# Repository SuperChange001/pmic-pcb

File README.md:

# Elastic Power Module

This repository contains the design and related files for the Elastic Power Module.

## Current Status
- [x] Schematic
- [x] PCB Design
- [x] Prototype
- [ ] Testing (** It is not tested yet, DO NOT use it as your reference design! **)
  - know issues:
    - in the default configuration, the nRST pin should be pulled up to VSYS, but right now it is floating.
      - should further check if I always need to have the external pull-up resistor or I can use the internal pull-up resistor of the microcontroller.
      - and how convinent it is to keep current circuit and configure the IC via microcontroller.
    - VIO should be connected to the header or a test pad, so we can configure the IC without flying a wire.

## Project Structure

- `elastic_power_module.kicad_pcb`: KiCad PCB design file.
- `elastic_power_module.kicad_prl`: KiCad project local settings file.
- `elastic_power_module.kicad_pro`: KiCad project file.
- `elastic_power_module.kicad_sch`: KiCad schematic file.
- `elastic_power_module.pdf`: PDF version of the schematic.
- `fp-info-cache`: Footprint info cache.
- `pictures`: Contains pictures of the assembled module.
  - `elastic_power_module_bottom_view.jpg`: Bottom view of the module.
  - `elastic_power_module_side_view.jpg`: Side view of the module.
  - `elastic_power_module_top_view.jpg`: Top view of the module.~

## Getting Started

- To get started with this project, clone the repository and open the `.kicad_pcb` or `.kicad_sch` files in KiCad.
- Or you can just download the PDF version of the schematic and use it as your reference design.
- To assemble the module, you can use the interactive BOM file [here](https://htmlpreview.github.io/?https://github.com/SuperChange001/pmic-pcb/blob/master/bom/ibom.html).

## Contributing

Contributions are welcome. Please open an issue to discuss your idea or submit a Pull Request.

## License

[MIT](https://choosealicense.com/licenses/mit/)~~~

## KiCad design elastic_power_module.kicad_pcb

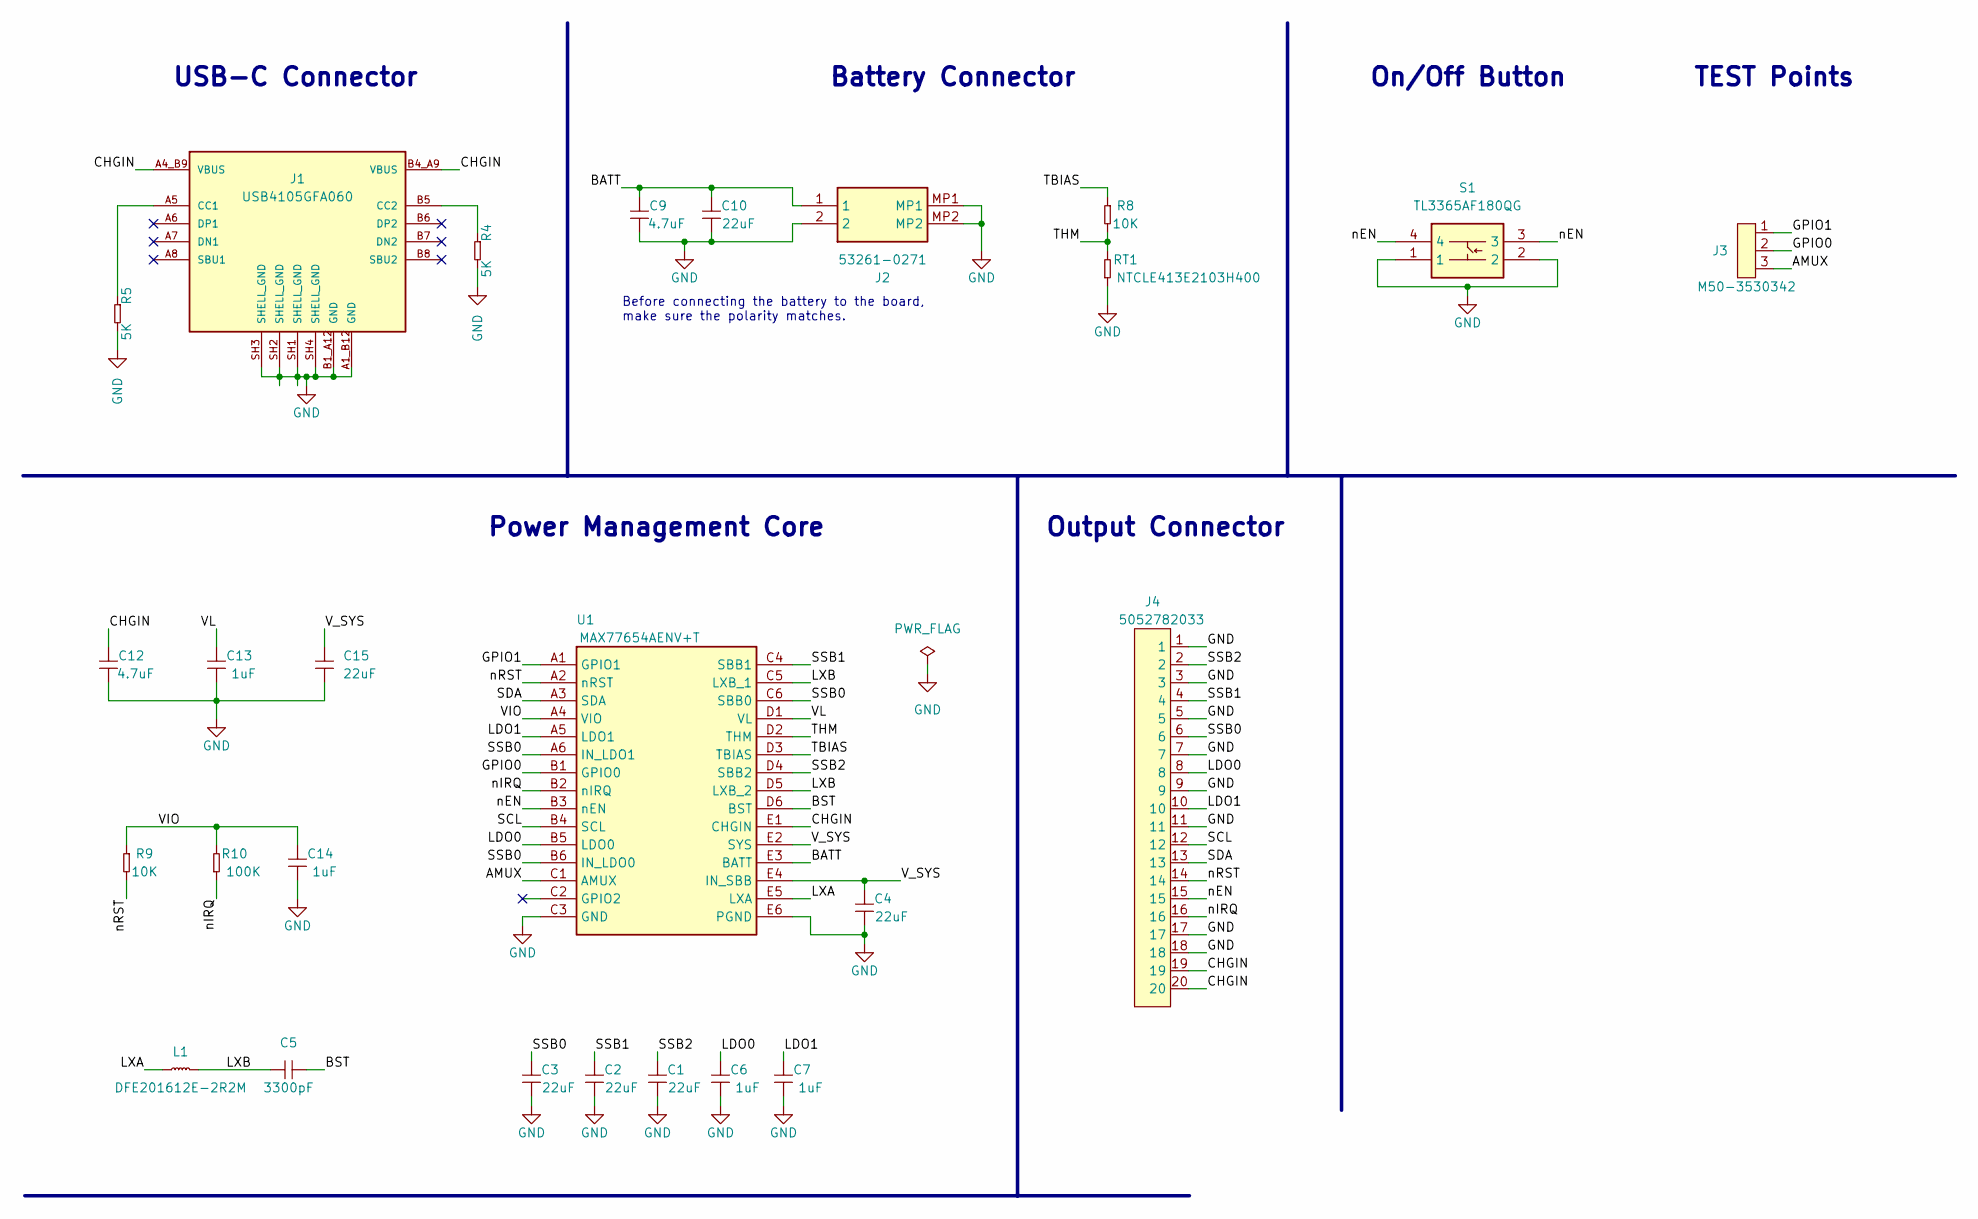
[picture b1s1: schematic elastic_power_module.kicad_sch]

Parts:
C1, C2, C3, C10, C15: 22uF; C_0402
C4: 22uF; C_0603
C5: 3300pF; C_0402
C6, C7, C13, C14: 1uF; C_0402
C9, C12: 4.7uF; C_0402
J1: USB4105GFA060; GCT_USB4105GFA060
J2: 53261-0271; Mouser Part Number 538-53261-0271
J3: M50-3530342; Header_THT_1.27_3P
J4: 5052782033; Connector_20PIN_5052782033
L1: DFE201612E-2R2M; L_0806
R4, R5: 5K; R_0402
R8, R9: 10K; R_0402
R10: 100K; R_0402
RT1: NTCLE413E2103H400; THT2
S1: TL3365AF180QG; Mouser Part Number 612-TL3365AF180QG
U1: MAX77654AENV+T; BGA30C40P6X5_279X234X50; Mouser Part Number 700-MAX77654AENV+T

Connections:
/AMUX: J3.3, U1.C1 (AMUX)
/BATT: C9.2, C10.1, J2.1, U1.E3 (BATT)
/BST: C5.1, U1.D6 (BST)
/CHGIN: C12.2, J1.A4_B9 (VBUS), J1.B4_A9 (VBUS), J4.19, J4.20, U1.E1 (CHGIN)
/GPIO0: J3.2, U1.B1 (GPIO0)
/GPIO1: J3.1, U1.A1 (GPIO1)
/LDO0: C6.1, J4.8, U1.B5 (LDO0)
/LDO1: C7.1, J4.10, U1.A5 (LDO1)
/LXA: L1.1, U1.E5 (LXA)
/LXB: C5.2, L1.2, U1.C5 (LXB_1), U1.D5 (LXB_2)
/SCL: J4.12, U1.B4 (SCL)
/SDA: J4.13, U1.A3 (SDA)
/SSB0: C3.1, J4.6, U1.A6 (IN_LDO1), U1.B6 (IN_LDO0), U1.C6 (SBB0)
/SSB1: C2.1, J4.4, U1.C4 (SBB1)
/SSB2: C1.1, J4.2, U1.D4 (SBB2)
/TBIAS: R8.2, U1.D3 (TBIAS)
/THM: R8.1, RT1.1, U1.D2 (THM)
/VIO: C14.1, R9.2, R10.1, U1.A4 (VIO)
/VL: C13.1, U1.D1 (VL)
/V_SYS: C4.1, C15.1, U1.E2 (SYS), U1.E4 (IN_SBB)
/nEN: J4.15, S1.3, S1.4, U1.B3 (nEN)
/nIRQ: J4.16, R10.2, U1.B2 (nIRQ)
/nRST: J4.14, R9.1, U1.A2 (nRST)
GND: C1.2, C2.2, C3.2, C4.2, C6.2, C7.2, C9.1, C10.2, C12.1, C13.2, C14.2, C15.2, J1.A1_B12 (GND), J1.B1_A12 (GND), J1.SH1 (SHELL_GND), J1.SH2 (SHELL_GND), J1.SH3 (SHELL_GND), J1.SH4 (SHELL_GND), J2.2, J2.MP1, J2.MP2, J4.1, J4.3, J4.5, J4.7, J4.9, J4.11, J4.17, J4.18, R4.1, R5.1, RT1.2, S1.1, S1.2, U1.C3 (GND), U1.E6 (PGND)
unnamed: J1.A5 (CC1), R5.2
unnamed: J1.B5 (CC2), R4.2

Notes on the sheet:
TEST Points
Output Connector
Battery Connector
USB-C Connector
On/Off Button
Power Management Core
Before connecting the battery to the board, make sure the polarity matches.

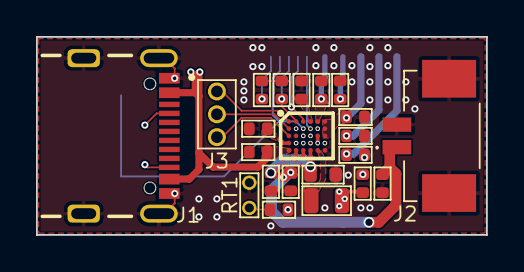
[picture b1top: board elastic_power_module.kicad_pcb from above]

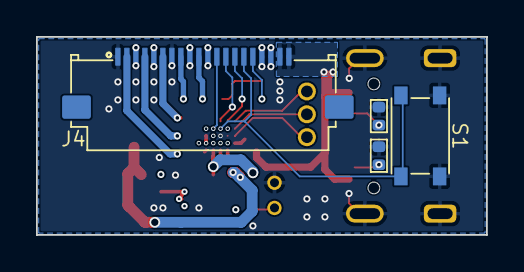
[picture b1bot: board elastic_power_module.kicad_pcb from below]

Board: 4 copper layers, 25.0 x 11.0 mm, 26 parts (4 on the bottom side), 26 nets.

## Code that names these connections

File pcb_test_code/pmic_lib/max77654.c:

#include "pico/stdlib.h"
#include "hardware/i2c.h"
#include "max77654.h"
#include "max77654_types.h"
#include <stdio.h>

#define __FILENAME__ (__builtin_strrchr(__FILE__, '/') ? __builtin_strrchr(__FILE__, '/') + 1 : __FILE__)
#define PRINT(fmt,...) {printf("[%s:%d <%s>]",__FILENAME__,__LINE__, __FUNCTION__); printf(fmt, ##__VA_ARGS__);printf("\n");}


#define MAX77654_SLAVE_ADDR 0x48
#define REG_ADDR_ERCFLAG 0x05
#define REG_ADDR_CNFG_SSBx_A 0x29 //0x29,0x2A for SSB0, 
#define REG_ADDR_CNFG_SSBx_B 0x2A //0x2B,0x2C for SSB1, 
                                  //0x2D,0x2E for SSB2

#define REG_ADDR_CNFG_LDOx_A 0x38 //0x38,0x39 for LDO0, 
#define REG_ADDR_CNFG_LDOx_B 0x39 //0x3A,0x3B for LDO1

#define OFF_IRRESPECTIVE_OF_FPS 0x04
#define ON_IRRESPECTIVE_OF_FPS 0x07


static i2c_inst_t *I2C_CH_MAX77654;
static reg_map_max77654_t reg_map_max77654;


typedef enum {
    TOVLD = 1 << 0,  // Thermal Overload
    SYSOVLO = 1 << 1,  // overvoltage-lockout
    SYSUVLO = 1 << 2,  // undervoltage-lockout
    // Add more error codes as needed
} ercflag_type;

uint8_t calculate_ssb_voltage_reg(int16_t voltage_in_mV)
{
    if(voltage_in_mV < 800)
        voltage_in_mV = 800;
    else if (voltage_in_mV > 5500)
        voltage_in_mV = 5500;

    int reg = 0;
    reg = (voltage_in_mV - 800) / 50;
    return reg;
}

uint8_t calculate_ldo_voltage_reg(int16_t voltage_in_mV)
{
    if(voltage_in_mV < 800)
        voltage_in_mV = 800;
    else if (voltage_in_mV > 3975)
        voltage_in_mV = 3975;

    int reg = 0;
    reg = (voltage_in_mV - 800) / 25;
    return reg;
}

void default_configure_max77654(void)
{
    reg_map_max77654.ssbs[0].reg_a.target_voltage = calculate_ssb_voltage_reg(3100);
    reg_map_max77654.ssbs[0].reg_b.enable_control = ON_IRRESPECTIVE_OF_FPS; // 0x00 = ON
    reg_map_max77654.ssbs[0].reg_b.active_discharge = 0x00; // 0x00 = Disable
    reg_map_max77654.ssbs[0].reg_b.peak_current_limit = 0x03; // 330mA
    reg_map_max77654.ssbs[0].reg_b.operation_mode = 0x00; // 0x00 = Buck-boost

    reg_map_max77654.ssbs[1].reg_a.target_voltage = calculate_ssb_voltage_reg(3200);
    reg_map_max77654.ssbs[1].reg_b.enable_control = ON_IRRESPECTIVE_OF_FPS; // 0x00 = ON
    reg_map_max77654.ssbs[1].reg_b.active_discharge = 0x00; // 0x00 = Disable
    reg_map_max77654.ssbs[1].reg_b.peak_current_limit = 0x03; // 330mA
    reg_map_max77654.ssbs[1].reg_b.operation_mode = 0x00; // 0x00 = Buck-boost

    reg_map_max77654.ssbs[2].reg_a.target_voltage = calculate_ssb_voltage_reg(3300);
    reg_map_max77654.ssbs[2].reg_b.enable_control = ON_IRRESPECTIVE_OF_FPS; // 0x00 = ON
    reg_map_max77654.ssbs[2].reg_b.active_discharge = 0x00; // 0x00 = Disable
    reg_map_max77654.ssbs[2].reg_b.peak_current_limit = 0x03; // 330mA
    reg_map_max77654.ssbs[2].reg_b.operation_mode = 0x00; // 0x00 = Buck-boost
   

    reg_map_max77654.ldos[0].reg_a.target_voltage = calculate_ldo_voltage_reg(1100); // set to 1100mV
    reg_map_max77654.ldos[0].reg_b.enable_control = ON_IRRESPECTIVE_OF_FPS; // 0x00 = ON
    reg_map_max77654.ldos[0].reg_b.active_discharge = 0x00; // 0x00 = Disable
    reg_map_max77654.ldos[0].reg_b.operation_mode = 0x00; // 0x00 = LDO

    reg_map_max77654.ldos[1].reg_a.target_voltage = calculate_ldo_voltage_reg(900); // set to 900mV
    reg_map_max77654.ldos[1].reg_b.enable_control = ON_IRRESPECTIVE_OF_FPS; // 0x00 = ON
    reg_map_max77654.ldos[1].reg_b.active_discharge = 0x00; // 0x00 = Disable
    reg_map_max77654.ldos[1].reg_b.operation_mode = 0x00; // 0x00 = LDO
}


int max77654_on_bus(void)
{
    int ret;
    uint8_t readbuffer[1];
    ret = i2c_read_blocking(I2C_CH_MAX77654, MAX77654_SLAVE_ADDR, readbuffer, 1, false);
    return ret;
}


int max77654_init(i2c_inst_t *i2c) 
{
    int ret;
    
    default_configure_max77654(); // does nothing but change the reg_map_max77654 on MCU

    I2C_CH_MAX77654 = i2c;

    i2c_init(i2c, 100 * 1000);
    gpio_set_function(26, GPIO_FUNC_I2C);
    gpio_set_function(27, GPIO_FUNC_I2C);
    gpio_pull_up(26);
    gpio_pull_up(27);

    ret = max77654_on_bus();
    if (ret < 0) 
    {
        return -1;
    }
    // PRINT("MAX77654 is on the bus\n");
    
    uint8_t cmd = REG_ADDR_ERCFLAG;
    i2c_write_blocking(I2C_CH_MAX77654, MAX77654_SLAVE_ADDR, &cmd, 1, false);
    
    ercflag_type erc;
    ret = i2c_read_blocking(I2C_CH_MAX77654, MAX77654_SLAVE_ADDR, &erc, 1, false);

    if (ret < 0) 
    {
        return -1;
    }
    else
    {   
        // PRINT("ERCFLAG: 0x%02x\n", erc);
        if (erc & TOVLD || erc & SYSOVLO || erc & SYSUVLO)
        {
             return -1;
        }
    }

    SSBx_set_voltage(0, 3100);
    SSBx_set_voltage(1, 3200);
    SSBx_set_voltage(2, 3300);
    SSBx_enable(0, true);
    SSBx_enable(1, true);
    SSBx_enable(2, true);

    LDOx_set_voltage(0, 1200);
    LDOx_set_voltage(1, 900);
    LDOx_enable(0, true);
    LDOx_enable(1, true);

    return 0;
}



int SSBx_enable(int ch, bool enable)
{
    uint8_t cmd[2];

    // first update the reg_map on MCU
    reg_map_max77654.ssbs[ch].reg_b.enable_control = enable ? ON_IRRESPECTIVE_OF_FPS : OFF_IRRESPECTIVE_OF_FPS;

    cmd[0] = REG_ADDR_CNFG_SSBx_B + ch * 2;
    cmd[1] = reg_map_max77654.ssbs[ch].reg_b.enable_control | (reg_map_max77654.ssbs[ch].reg_b.active_discharge<<3) | (reg_map_max77654.ssbs[ch].reg_b.peak_current_limit<<4) | (reg_map_max77654.ssbs[ch].reg_b.operation_mode<<5);
    i2c_write_blocking(I2C_CH_MAX77654, MAX77654_SLAVE_ADDR, cmd, 2, false);

    PRINT("SSB%d %s", ch, enable ? "enabled" : "disabled\n");
    PRINT("%02x %02x\n", cmd[0], cmd[1]);
    return 0;
}

int SSBx_set_voltage(int ch, int16_t voltage_in_mV)
{
    uint8_t cmd[2];

    // first update the reg_map on MCU
    reg_map_max77654.ssbs[ch].reg_a.target_voltage = calculate_ssb_voltage_reg(voltage_in_mV);

    cmd[0] = REG_ADDR_CNFG_SSBx_A + ch * 2;
    cmd[1] = reg_map_max77654.ssbs[ch].reg_a.target_voltage;
    i2c_write_blocking(I2C_CH_MAX77654, MAX77654_SLAVE_ADDR, cmd, 2, false);
    PRINT("SSB%d voltage set to %d mV", ch, voltage_in_mV);
    PRINT("%02x %02x\n", cmd[0], cmd[1]);
    return 0;
}

int LDOx_set_mode(int ch, int mode)
{
    uint8_t cmd[2];
    
    reg_map_max77654.ldos[ch].reg_b.operation_mode = mode;
    
    cmd[0] = REG_ADDR_CNFG_LDOx_B + ch * 2;
    cmd[1] = reg_map_max77654.ldos[ch].reg_b.operation_mode|(reg_map_max77654.ldos[ch].reg_b.active_discharge<<3)|(reg_map_max77654.ldos[ch].reg_b.operation_mode<<4);
    i2c_write_blocking(I2C_CH_MAX77654, MAX77654_SLAVE_ADDR, cmd, 2, false);
    // PRINT("SSB%d %s", ch, enable ? "enabled" : "disabled\n");
    // PRINT("%02x %02x\n", cmd[0], cmd[1]);
    return 0;
}

int LDOx_enable_active_discharge(int ch, bool enable)
{
    uint8_t cmd[2];

    reg_map_max77654.ldos[ch].reg_b.active_discharge = enable ? ON_IRRESPECTIVE_OF_FPS : OFF_IRRESPECTIVE_OF_FPS;

    cmd[0] = REG_ADDR_CNFG_LDOx_B + ch * 2;
    cmd[1] = reg_map_max77654.ldos[ch].reg_b.operation_mode|(reg_map_max77654.ldos[ch].reg_b.active_discharge<<3)|(reg_map_max77654.ldos[ch].reg_b.operation_mode<<4);
    
    i2c_write_blocking(I2C_CH_MAX77654, MAX77654_SLAVE_ADDR, cmd, 2, false);
    // PRINT("SSB%d %s", ch, enable ? "enabled" : "disabled\n");
    // PRINT("%02x %02x\n", cmd[0], cmd[1]);
    return 0;
}

int LDOx_enable(int ch, bool enable)
{
    uint8_t cmd[2];

    reg_map_max77654.ldos[ch].reg_b.enable_control = enable ? ON_IRRESPECTIVE_OF_FPS : OFF_IRRESPECTIVE_OF_FPS;

    cmd[0] = REG_ADDR_CNFG_LDOx_B + ch * 2;
    cmd[1] = reg_map_max77654.ldos[ch].reg_b.operation_mode|(reg_map_max77654.ldos[ch].reg_b.active_discharge<<3)|(reg_map_max77654.ldos[ch].reg_b.operation_mode<<4);
    
    i2c_write_blocking(I2C_CH_MAX77654, MAX77654_SLAVE_ADDR, cmd, 2, false);
    // PRINT("SSB%d %s", ch, enable ? "enabled" : "disabled\n");
    // PRINT("%02x %02x\n", cmd[0], cmd[1]);
    return 0;
}

int LDOx_set_voltage(int ch, int16_t voltage_in_mV)
{
    uint8_t cmd[2];

    // first update the reg_map on MCU
    reg_map_max77654.ldos[ch].reg_a.target_voltage = calculate_ldo_voltage_reg(voltage_in_mV);

    cmd[0] = REG_ADDR_CNFG_LDOx_A + ch * 2;
    cmd[1] = reg_map_max77654.ldos[ch].reg_a.target_voltage;
    i2c_write_blocking(I2C_CH_MAX77654, MAX77654_SLAVE_ADDR, cmd, 2, false);
    PRINT("LDO%d voltage set to %d mV", ch, voltage_in_mV);
    PRINT("%02x %02x\n", cmd[0], cmd[1]);
    return 0;
}

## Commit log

2023-12-18 half way of the prototype
2023-12-18 schematic finished
2023-12-19 layout almost finished
2023-12-20 almost done the PCB
2024-01-11 backup
2024-01-11 done ;).
2024-01-11 optimize footprints
2024-01-11 add bom
2024-01-11 add ignore
2024-01-11 remove useless files
2024-01-11 update pcb file
2024-01-11 update gitignore
2024-01-11 update schematic
2024-01-11 create empty readme
2024-01-11 add read me
2024-01-11 optimise readme
2024-02-04 add known issue
2024-03-27 add tested code, and the PMIC board works, but needs improvements
